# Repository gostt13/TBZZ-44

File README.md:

# TBZZ-44
Ergonomic keyboard inspired by Jorne/Corne
Split-keyboard

This repository includes Pcb, Top plate and bottom plate.
Firmware from https://github.com/joric/jorne

- More simple version and Wireless friendly

- No rgb, however, more cheaper!

- My first project with Using Kicad

- Made in KiCad

References
- https://github.com/joric/jorne

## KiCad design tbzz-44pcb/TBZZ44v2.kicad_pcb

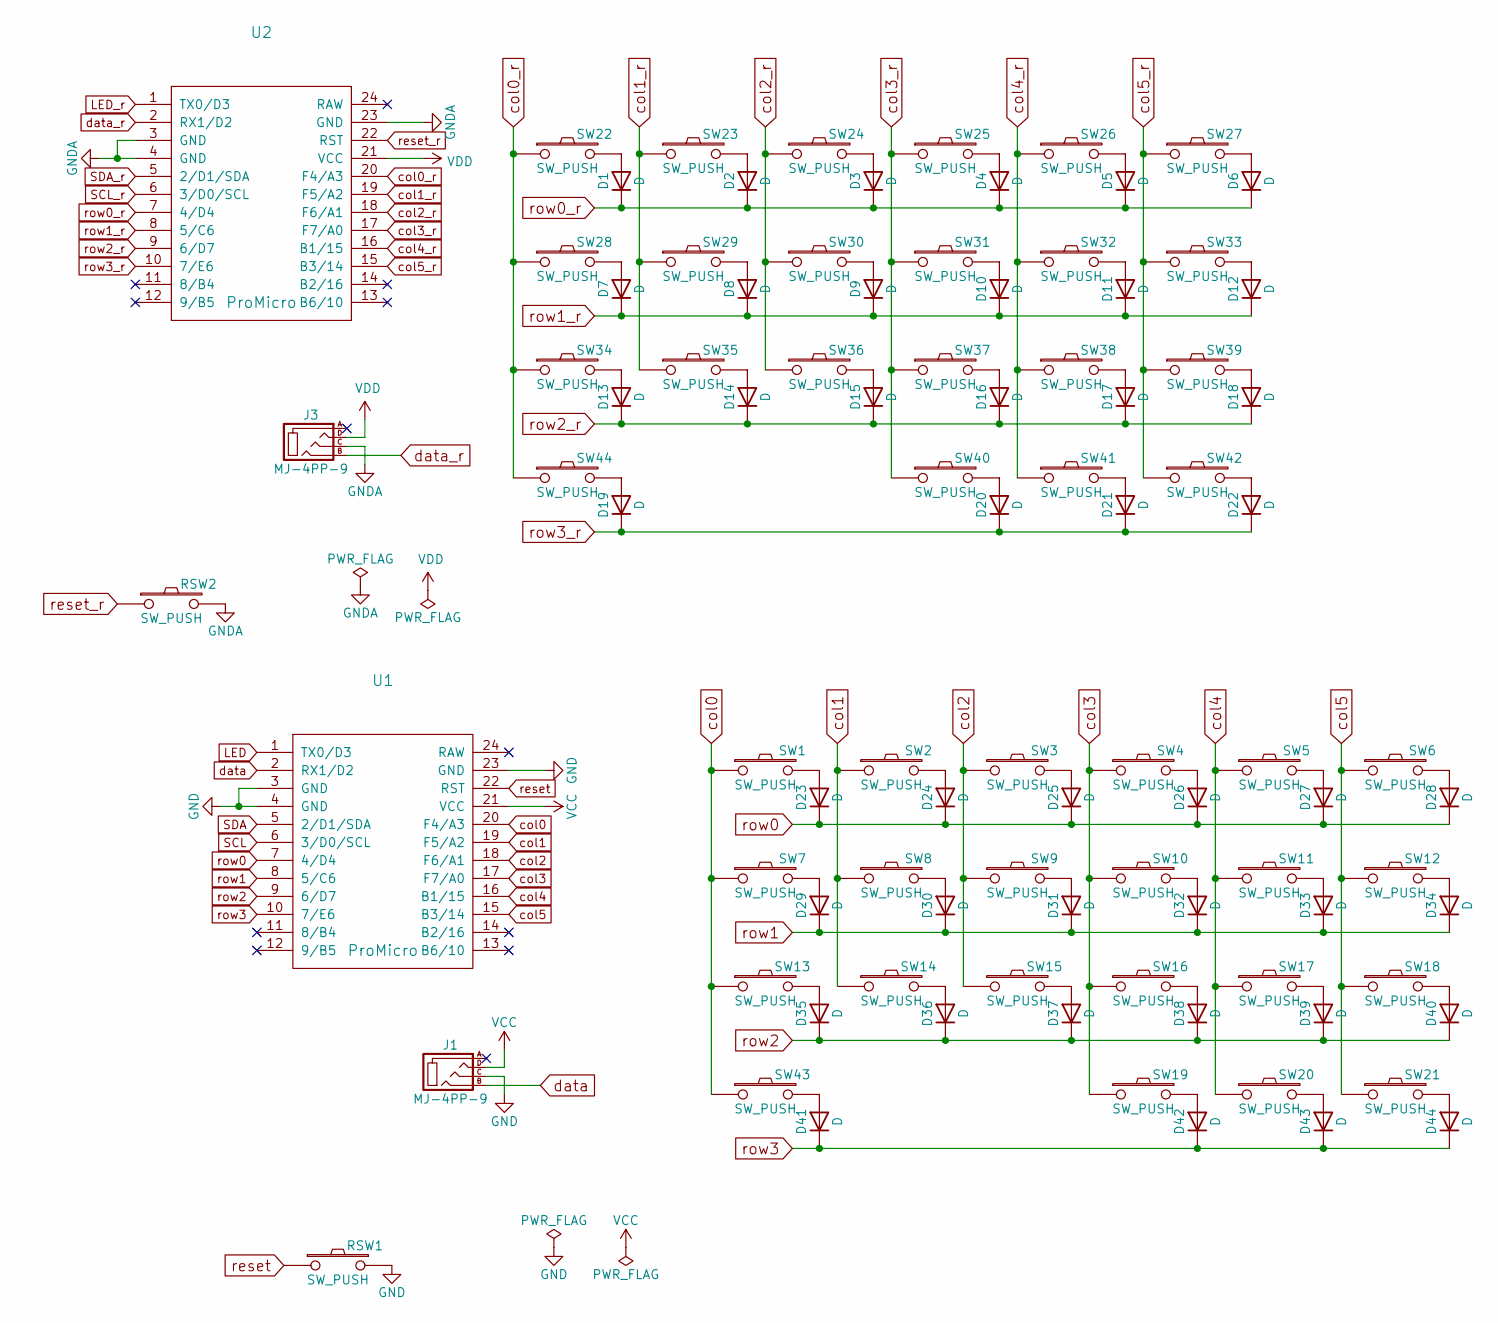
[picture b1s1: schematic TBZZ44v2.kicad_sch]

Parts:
D1, D2, D3, D4, D5, D6, D7, D8, D9, D10, D11, D12, D13, D14, D15, D16, D17, D18, D19, D20, D21, D22, D23, D24, D25, D26, D27, D28, D29, D30, D31, D32, D33, D34, D35, D36, D37, D38, D39, D40, D41, D42, D43, D44: D; D3_SMD_v2
J1, J3: MJ-4PP-9; MJ-4PP-9_1side
RSW1, RSW2: SW_PUSH; ResetSW_1side
SW1, SW2, SW3, SW4, SW5, SW6, SW7, SW8, SW9, SW10, SW11, SW12, SW13, SW14, SW15, SW16, SW17, SW18, SW19, SW20, SW22, SW23, SW24, SW25, SW26, SW27, SW28, SW29, SW30, SW31, SW32, SW33, SW34, SW35, SW36, SW37, SW38, SW39, SW40, SW41, SW43, SW44: SW_PUSH; CherryMX_Hotswap
SW21, SW42: SW_PUSH; CherryMX_Hotswap_1.5u
U1, U2: ProMicro; ProMicro_v3

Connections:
GND: J1.C, RSW1.2, U1.3 (GND), U1.4 (GND), U1.23 (GND)
GNDA: J3.C, RSW2.2, U2.3 (GND), U2.4 (GND), U2.23 (GND)
LED: U1.1 (TX0/D3)
LED_r: U2.1 (TX0/D3)
unnamed: D23.2 (A), SW1.2
unnamed: D24.2 (A), SW2.2
unnamed: D25.2 (A), SW3.2
unnamed: D26.2 (A), SW4.2
unnamed: D27.2 (A), SW5.2
unnamed: D28.2 (A), SW6.2
unnamed: D29.2 (A), SW7.2
unnamed: D30.2 (A), SW8.2
unnamed: D31.2 (A), SW9.2
unnamed: D32.2 (A), SW10.2
unnamed: D33.2 (A), SW11.2
unnamed: D34.2 (A), SW12.2
unnamed: D35.2 (A), SW13.2
unnamed: D36.2 (A), SW14.2
unnamed: D37.2 (A), SW15.2
unnamed: D38.2 (A), SW16.2
unnamed: D39.2 (A), SW17.2
unnamed: D40.2 (A), SW18.2
unnamed: D42.2 (A), SW19.2
unnamed: D43.2 (A), SW20.2
unnamed: D44.2 (A), SW21.2
unnamed: D1.2 (A), SW22.2
unnamed: D2.2 (A), SW23.2
unnamed: D3.2 (A), SW24.2
unnamed: D4.2 (A), SW25.2
unnamed: D5.2 (A), SW26.2
unnamed: D6.2 (A), SW27.2
unnamed: D7.2 (A), SW28.2
unnamed: D8.2 (A), SW29.2
unnamed: D9.2 (A), SW30.2
unnamed: D10.2 (A), SW31.2
unnamed: D11.2 (A), SW32.2
unnamed: D12.2 (A), SW33.2
unnamed: D13.2 (A), SW34.2
unnamed: D14.2 (A), SW35.2
unnamed: D15.2 (A), SW36.2
unnamed: D16.2 (A), SW37.2
unnamed: D17.2 (A), SW38.2
unnamed: D18.2 (A), SW39.2
unnamed: D20.2 (A), SW40.2
unnamed: D21.2 (A), SW41.2
unnamed: D22.2 (A), SW42.2
unnamed: D41.2 (A), SW43.2
unnamed: D19.2 (A), SW44.2
SCL: U1.6 (3/D0/SCL)
SCL_r: U2.6 (3/D0/SCL)
SDA: U1.5 (2/D1/SDA)
SDA_r: U2.5 (2/D1/SDA)
VCC: J1.D, U1.21 (VCC)
VDD: J3.D, U2.21 (VCC)
col0: SW1.1, SW7.1, SW13.1, SW43.1, U1.20 (F4/A3)
col0_r: SW22.1, SW28.1, SW34.1, SW44.1, U2.20 (F4/A3)
col1: SW2.1, SW8.1, SW14.1, U1.19 (F5/A2)
col1_r: SW23.1, SW29.1, SW35.1, U2.19 (F5/A2)
col2: SW3.1, SW9.1, SW15.1, U1.18 (F6/A1)
col2_r: SW24.1, SW30.1, SW36.1, U2.18 (F6/A1)
col3: SW4.1, SW10.1, SW16.1, SW19.1, U1.17 (F7/A0)
col3_r: SW25.1, SW31.1, SW37.1, SW40.1, U2.17 (F7/A0)
col4: SW5.1, SW11.1, SW17.1, SW20.1, U1.16 (B1/15)
col4_r: SW26.1, SW32.1, SW38.1, SW41.1, U2.16 (B1/15)
col5: SW6.1, SW12.1, SW18.1, SW21.1, U1.15 (B3/14)
col5_r: SW27.1, SW33.1, SW39.1, SW42.1, U2.15 (B3/14)
data: J1.B, U1.2 (RX1/D2)
data_r: J3.B, U2.2 (RX1/D2)
reset: RSW1.1, U1.22 (RST)
reset_r: RSW2.1, U2.22 (RST)
row0: D23.1 (K), D24.1 (K), D25.1 (K), D26.1 (K), D27.1 (K), D28.1 (K), U1.7 (4/D4)
row0_r: D1.1 (K), D2.1 (K), D3.1 (K), D4.1 (K), D5.1 (K), D6.1 (K), U2.7 (4/D4)
row1: D29.1 (K), D30.1 (K), D31.1 (K), D32.1 (K), D33.1 (K), D34.1 (K), U1.8 (5/C6)
row1_r: D7.1 (K), D8.1 (K), D9.1 (K), D10.1 (K), D11.1 (K), D12.1 (K), U2.8 (5/C6)
row2: D35.1 (K), D36.1 (K), D37.1 (K), D38.1 (K), D39.1 (K), D40.1 (K), U1.9 (6/D7)
row2_r: D13.1 (K), D14.1 (K), D15.1 (K), D16.1 (K), D17.1 (K), D18.1 (K), U2.9 (6/D7)
row3: D41.1 (K), D42.1 (K), D43.1 (K), D44.1 (K), U1.10 (7/E6)
row3_r: D19.1 (K), D20.1 (K), D21.1 (K), D22.1 (K), U2.10 (7/E6)

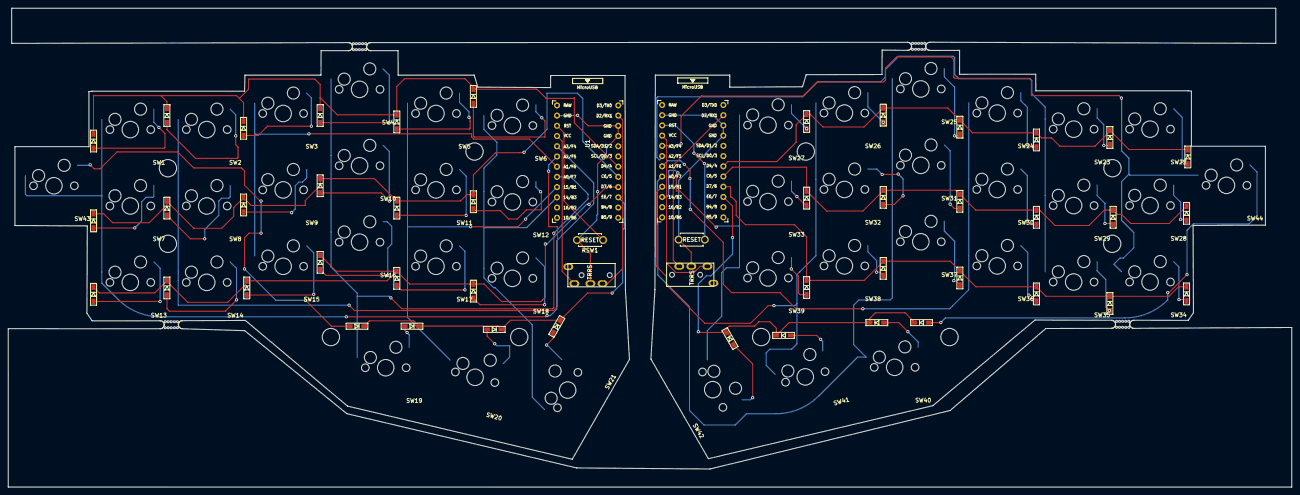
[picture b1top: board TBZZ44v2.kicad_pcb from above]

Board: 2 copper layers, 319.1 x 119.1 mm, 108 parts (0 on the bottom side), 72 nets.

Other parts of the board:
Ref**: Val**; M2_HOLE_v2
Ref**#2, Ref**#3, Ref**#4, Ref**#5, Ref**#6, Ref**#7, Ref**#8, Ref**#9, Ref**#10: Val**; M2_HOLE_v2
mouse-bite-3mm-slot, mouse-bite-3mm-slot#2, mouse-bite-3mm-slot#3, mouse-bite-3mm-slot#4: VAL**; mouse-bite-3mm-slot
